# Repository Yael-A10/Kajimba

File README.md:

# Kajimba Pump

## Installation

---

1. Install [MicroPython](https://micropython.org/) on the **Raspberry Pi Pico**: [*Instructions*](https://www.raspberrypi.com/documentation/microcontrollers/micropython.html)
2. Move all the python files from the [`Python` folder](https://github.com/Yael-A10/Kajimba/tree/main/Python) onto the **Raspberry Pi Pico**, including the `logs.txt` file. To do this:
    - Install [Thonny](https://thonny.org/)
    - Once it's installed open it and plug in the **Raspberry Pi Pico** to your computer
    - Select `Raspberry Pi Pico` as your device in the bottom right corner of the [Thonny](https://thonny.org/) software.
    - Next click `file>open` and select `This computer` as the device to open from. Then open all the files you want to upload to the **Raspberry Pi Pico**.
    - For each file click `file>Save as...` and select `Raspberry Pi Pico` as the device to save to.

If all was done correctly the program should start running as soon as the **Raspberry Pi Pico** is powered.

## User guide

---

1. In the `main.py` file, change/add `mosfet` and `flowSensor` pins depending on how many pump/flowSensor pairs you have. These are the default pins:

    ```python
    #define the pump and flow sensor pins:
    mosfet1 = 19
    flowSensor1 = 8
    ```

2. If you added more pump/flowSensor pairs, create a new `pair` variable with your new `mosfet` and `flowSensor` pins and add it to `pairList`. This is the default pair:

    ```python
    #create the pump and flow sensor pairs:
    pair1 = pumpSensorPairs(mosfet1, flowSensor1)

    #add the pairs into the pair list
    pairList = [pair1]
    ```

3. Change the `ml1` and `ml2` values depending on the values needed, these are the default values:

    ```python
    #variables
    ml1 = 285
    ml2 = 300
    ```

4. Change the `percentToStartSlowing` value to a value between 0 and 90. This variable represents the percentage of the bottle that is filled and the pump(s) will start slowing down after that percent is reached. This is the default value:

    ```python
    percentToStartSlowing = 75 #variable set between 0 and 90 that controls when the pump(s) start slowing down
    ```

Once the **Raspberry Pi Pico** is powered it will automatically run `main.py`. If the display is connected it will:

- Ask the user if they want to run a test (which will run the **pump(s)** for 10 seconds and test if the **flow sensor(s)** gets any output (10 ml))

    - If you want to run the test, hold down the button for 3 seconds.
    - If not, press the button once and it will skip the test.

If the display is not connected, it will skip this test and move on directly to the next part:

- To choose between the preset `ml1` and `ml2` amounts to fill:
    - Press the button once to choose `ml1`
    - Hold down the button for 3 seconds to choose `ml2`
- To run the pump(s) you have two options:
    - To run the pump(s) indefinately hold down the button for 3 seconds. Press it again to stop.
    - To run the pump(s) for the set amount of `ml`, press the button once. The pump(s) will slow down incrementally as the bottle gets filled.

    > Note that you can press the button again at anytime to make the pump(s) stop running.

When the display is connected, it will display the amount of times a bottle was filled during the session (top value) and the total amount of times a bottle was filled (bottom value):

```
Filled: ()
Total: ()
```

The total amount of times a bottle was filled is stored on `logs.txt`, you can edit this value if you want to edit/reset the total amount of bottles filled.

## KiCad

---

Here is the unpopulated **PCB**:

Here is the populated **PCB**:

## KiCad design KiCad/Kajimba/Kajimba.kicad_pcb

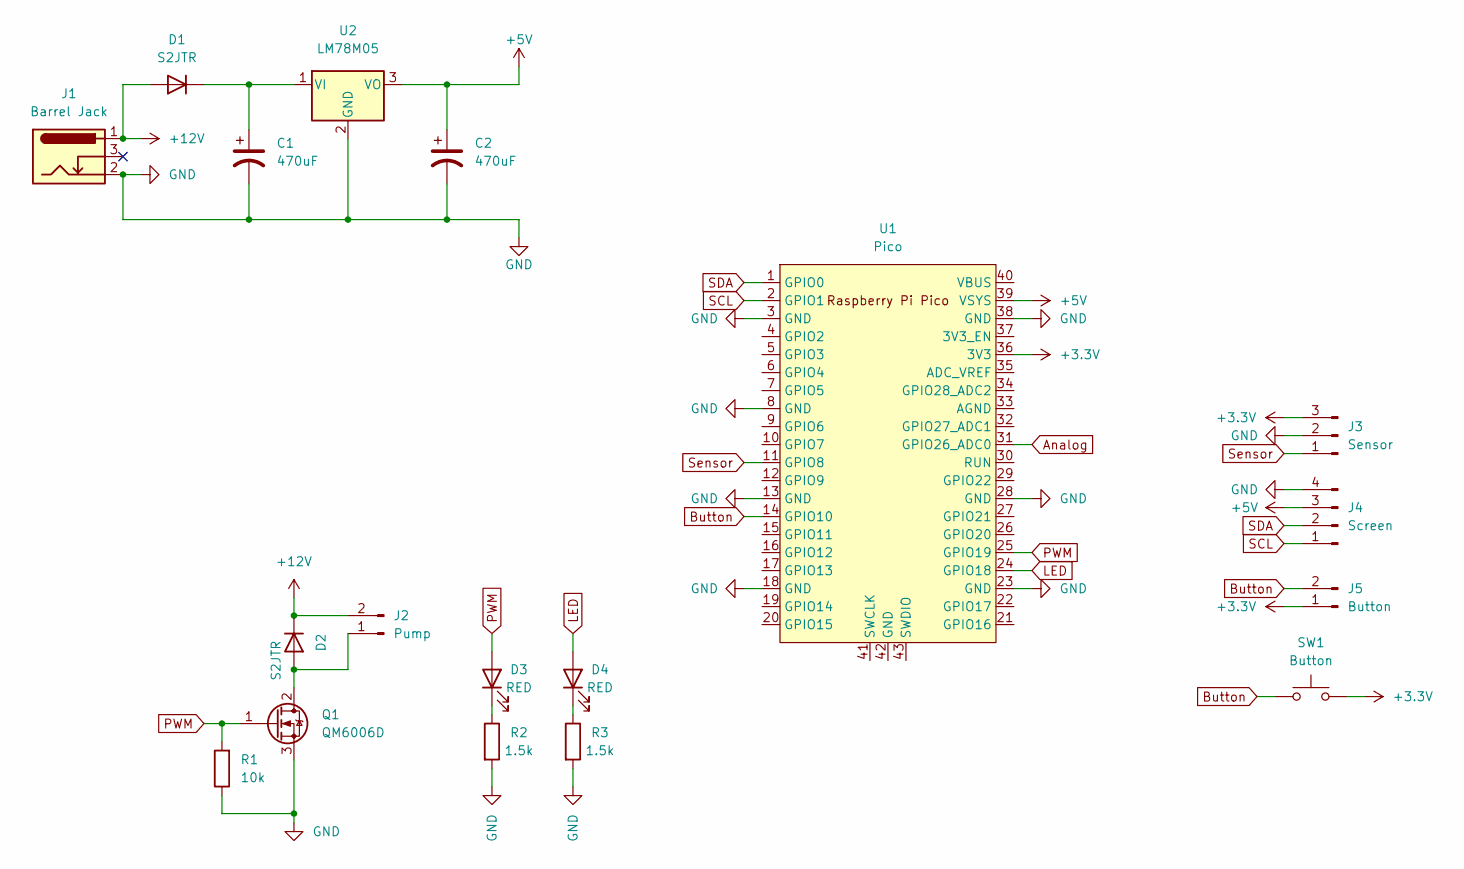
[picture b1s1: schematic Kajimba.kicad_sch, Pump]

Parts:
C1, C2: 470uF; CP_Elec_10x10.5
D1, D2: S2JTR; D_SMB
D3, D4: RED; LED_0805_2012Metric_Pad1.15x1.40mm_HandSolder
J1: Barrel Jack; BarrelJack_Wuerth_6941xx301002
J2: Pump; PhoenixContact_MSTBA_2,5_2-G-5,08_1x02_P5.08mm_Horizontal
J3: Sensor; JST_EH_B3B-EH-A_1x03_P2.50mm_Vertical
J4: Screen; JST_EH_B4B-EH-A_1x04_P2.50mm_Vertical
J5: Button; JST_EH_B2B-EH-A_1x02_P2.50mm_Vertical
Q1: QM6006D; TO-252-2
R1: 10k; R_0805_2012Metric_Pad1.20x1.40mm_HandSolder
R2, R3: 1.5k; R_0805_2012Metric_Pad1.20x1.40mm_HandSolder
SW1: Button; SW_SPST_TL3305A
U1: Pico; RPi_Pico_SMD_TH
U2: LM78M05; TO-252-2

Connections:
+3.3V: J3.3, J5.1, SW1.2, U1.36 (3V3)
+5V: C2.1, J4.3, U1.39 (VSYS), U2.3 (VO)
+12V: D1.2 (A), D2.1 (K), J1.1, J2.2
Analog: U1.31 (GPIO26_ADC0)
Button: J5.2, SW1.1, U1.14 (GPIO10)
GND: C1.2, C2.2, J1.2, J3.2, J4.4, Q1.3 (S), R1.1, R2.2, R3.2, U1.3 (GND), U1.8 (GND), U1.13 (GND), U1.18 (GND), U1.23 (GND), U1.28 (GND), U1.38 (GND), U2.2 (GND)
LED: D4.2 (A), U1.24 (GPIO18)
unnamed: C1.1, D1.1 (K), U2.1 (VI)
unnamed: D2.2 (A), J2.1, Q1.2 (D)
unnamed: D3.1 (K), R2.1
unnamed: D4.1 (K), R3.1
PWM: D3.2 (A), Q1.1 (G), R1.2, U1.25 (GPIO19)
SCL: J4.1, U1.2 (GPIO1)
SDA: J4.2, U1.1 (GPIO0)
Sensor: J3.1, U1.11 (GPIO8)

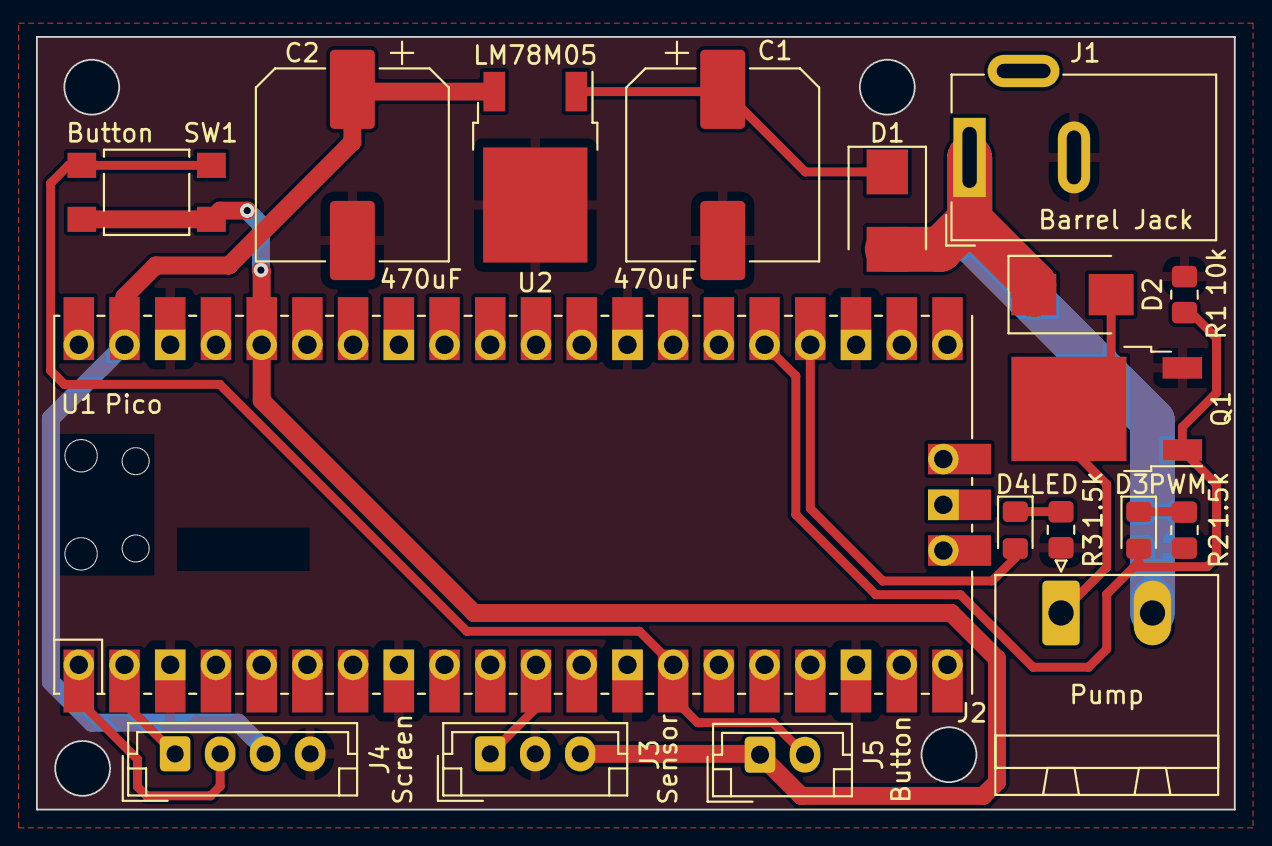
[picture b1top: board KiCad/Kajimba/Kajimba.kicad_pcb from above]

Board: 2 copper layers, 66.5 x 42.9 mm, 18 parts (0 on the bottom side), 14 nets.

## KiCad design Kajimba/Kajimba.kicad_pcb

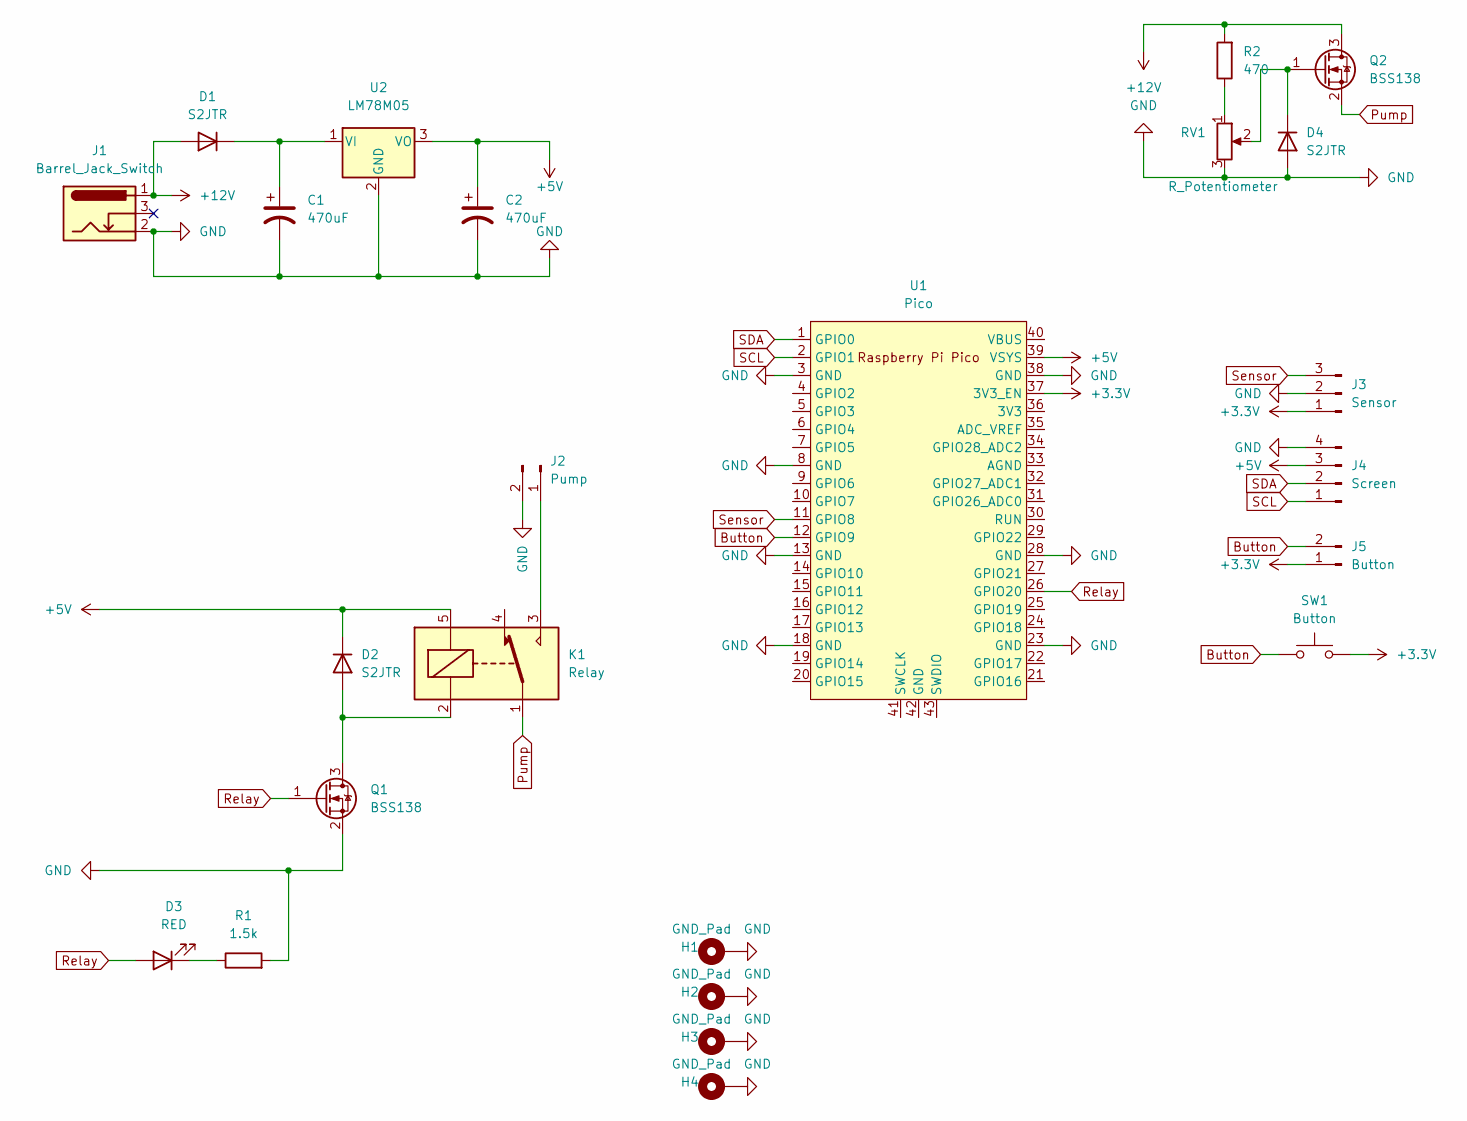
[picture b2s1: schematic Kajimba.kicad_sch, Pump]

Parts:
C1, C2: 470uF; CP_Elec_10x10.5
D1, D2, D4: S2JTR; D_SMB
D3: RED; LED_0805_2012Metric_Pad1.15x1.40mm_HandSolder
H1, H2, H3, H4: GND_Pad; MountingHole_2.2mm_M2_Pad
J1: Barrel_Jack_Switch; BarrelJack_Wuerth_6941xx301002
J2: Pump; PhoenixContact_MSTBA_2,5_2-G-5,08_1x02_P5.08mm_Horizontal
J3: Sensor; JST_EH_B3B-EH-A_1x03_P2.50mm_Vertical
J4: Screen; JST_EH_B4B-EH-A_1x04_P2.50mm_Vertical
J5: Button; JST_EH_B2B-EH-A_1x02_P2.50mm_Vertical
K1: Relay; Relay_SPDT_SANYOU_SRD_Series_Form_C
Q1, Q2: BSS138; SOT-23_Handsoldering
R1: 1.5k; R_0805_2012Metric_Pad1.20x1.40mm_HandSolder
R2: 470; R_0805_2012Metric_Pad1.20x1.40mm_HandSolder
RV1: R_Potentiometer; Potentiometer_Bourns_3296W_Vertical
SW1: Button; SW_SPST_TL3305A
U1: Pico; RPi_Pico_SMD_TH
U2: LM78M05; TO-252-2

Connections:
+3.3V: J3.1, J5.1, SW1.2, U1.37 (3V3_EN)
+5V: C2.1, D2.1 (K), J4.3, K1.5, U1.39 (VSYS), U2.3 (VO)
+12V: D1.2 (A), J1.1, Q2.3 (D), R2.2
Button: J5.2, SW1.1, U1.12 (GPIO9)
GND: C1.2, C2.2, D4.2 (A), H1.1, H2.1, H3.1, H4.1, J1.2, J2.2, J3.2, J4.4, Q1.2 (S), R1.2, RV1.3, U1.3 (GND), U1.8 (GND), U1.13 (GND), U1.18 (GND), U1.23 (GND), U1.28 (GND), U1.38 (GND), U2.2 (GND)
unnamed: C1.1, D1.1 (K), U2.1 (VI)
unnamed: D2.2 (A), K1.2, Q1.3 (D)
unnamed: D3.1 (K), R1.1
unnamed: D4.1 (K), Q2.1 (G), RV1.2
unnamed: J2.1, K1.3
unnamed: R2.1, RV1.1
Pump: K1.1, Q2.2 (S)
Relay: D3.2 (A), Q1.1 (G), U1.26 (GPIO20)
SCL: J4.1, U1.2 (GPIO1)
SDA: J4.2, U1.1 (GPIO0)
Sensor: J3.3, U1.11 (GPIO8)

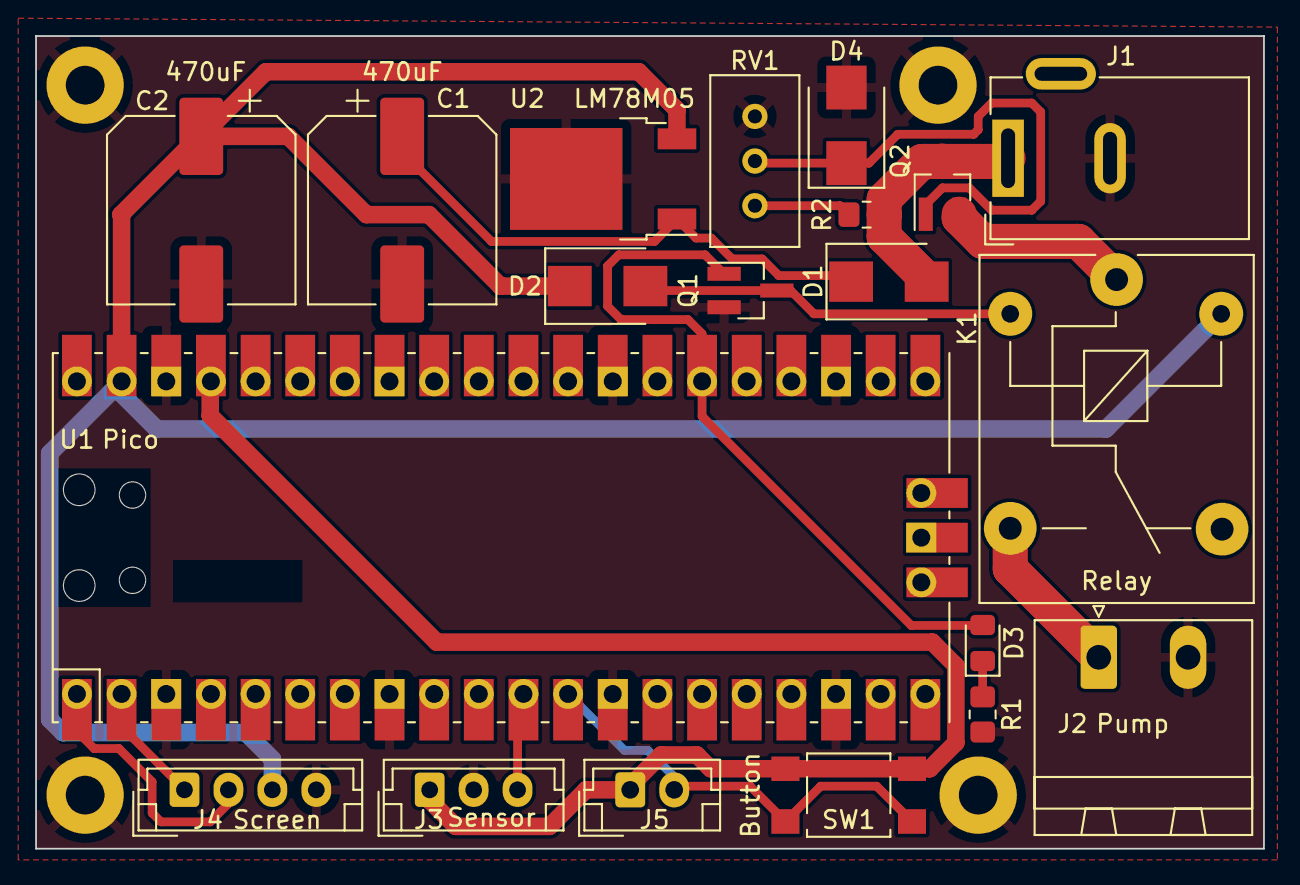
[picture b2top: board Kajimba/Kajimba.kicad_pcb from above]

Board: 2 copper layers, 69.8 x 46.2 mm, 24 parts (0 on the bottom side), 16 nets.

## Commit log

2022-12-06 Create kicad.gitignore
    Created kicad.gitignore
2022-12-06 KiCad Pump PCB v01
2022-12-06 KiCad PCB Pump v01.1
2022-12-06 KiCad PCB Pump v02
2022-12-06 KiCad PCB Pump v03
2022-12-06 KiCad PCB Pump v04
2022-12-06 3d models + python into folder
2022-12-06 New KiCad Folder
2022-12-06 KiCad Folder Update
    Added Kajimba Gerbers plus Kajimba Backup Folders and files from USB stick
2022-12-06 Small update
2022-12-06 main.py Cleanup
    -pumpGroup made into dictionary
    -separated main loop into functions
    -better variable naming
2022-12-06 Revert "Update .DS_Store"
    This reverts commit da4d2dd8f873dbebc9d6f65310222f786067e4fb.
2022-12-07 Cleanup
2022-12-22 v05
    moved pin 3.3v_en to 3.3v
    switched pins on 3 pin jst connector
    cleaned up circuit diagram sheet
2022-12-30 main.py update
    - Updated code for mosfet functionality
    - Updated the pins for button and flow sensor
2023-01-10 Python
2023-01-18 v06 KiCad
    removed pot
    moved button / IO around
2023-01-31 Python main.py update
    fixed button glitches
    cleaned up code
    added tester
2023-01-31 fixing commit errors
2023-01-31 Update gitignore
2023-02-01 major python update
    - divided code into different files
    - changed pumpGroups dictionary into pumpSensorPairs class
    - fixed .gitignore file
    - fixed python bugs
2023-02-01 removing ignored files
2023-02-01 minor changes to kicad files
2023-02-02 Modified README file and added logs.txt
2023-02-02 Python file update
    - removed unnecessary files
    - started using interrupt handler instead of old method
    - updated some functions to be more descriptive
    - added functionality to buttonManager.py (added holdButton function)
    - modified README.md
2023-02-02 Images
2023-02-02 image
2023-02-05 python improvements
    improvements to the pumpManager:
    - added function to switch on pumps with time delay
    - added function to switch off all pumps
    - added feature that pumps only start slowing down after bottle is 75 percent full
2023-02-06 python changes
    added variable for when the pump(s) should start slowing down
2023-02-10 minor python updates
    added ml chooser
    changed if statements
